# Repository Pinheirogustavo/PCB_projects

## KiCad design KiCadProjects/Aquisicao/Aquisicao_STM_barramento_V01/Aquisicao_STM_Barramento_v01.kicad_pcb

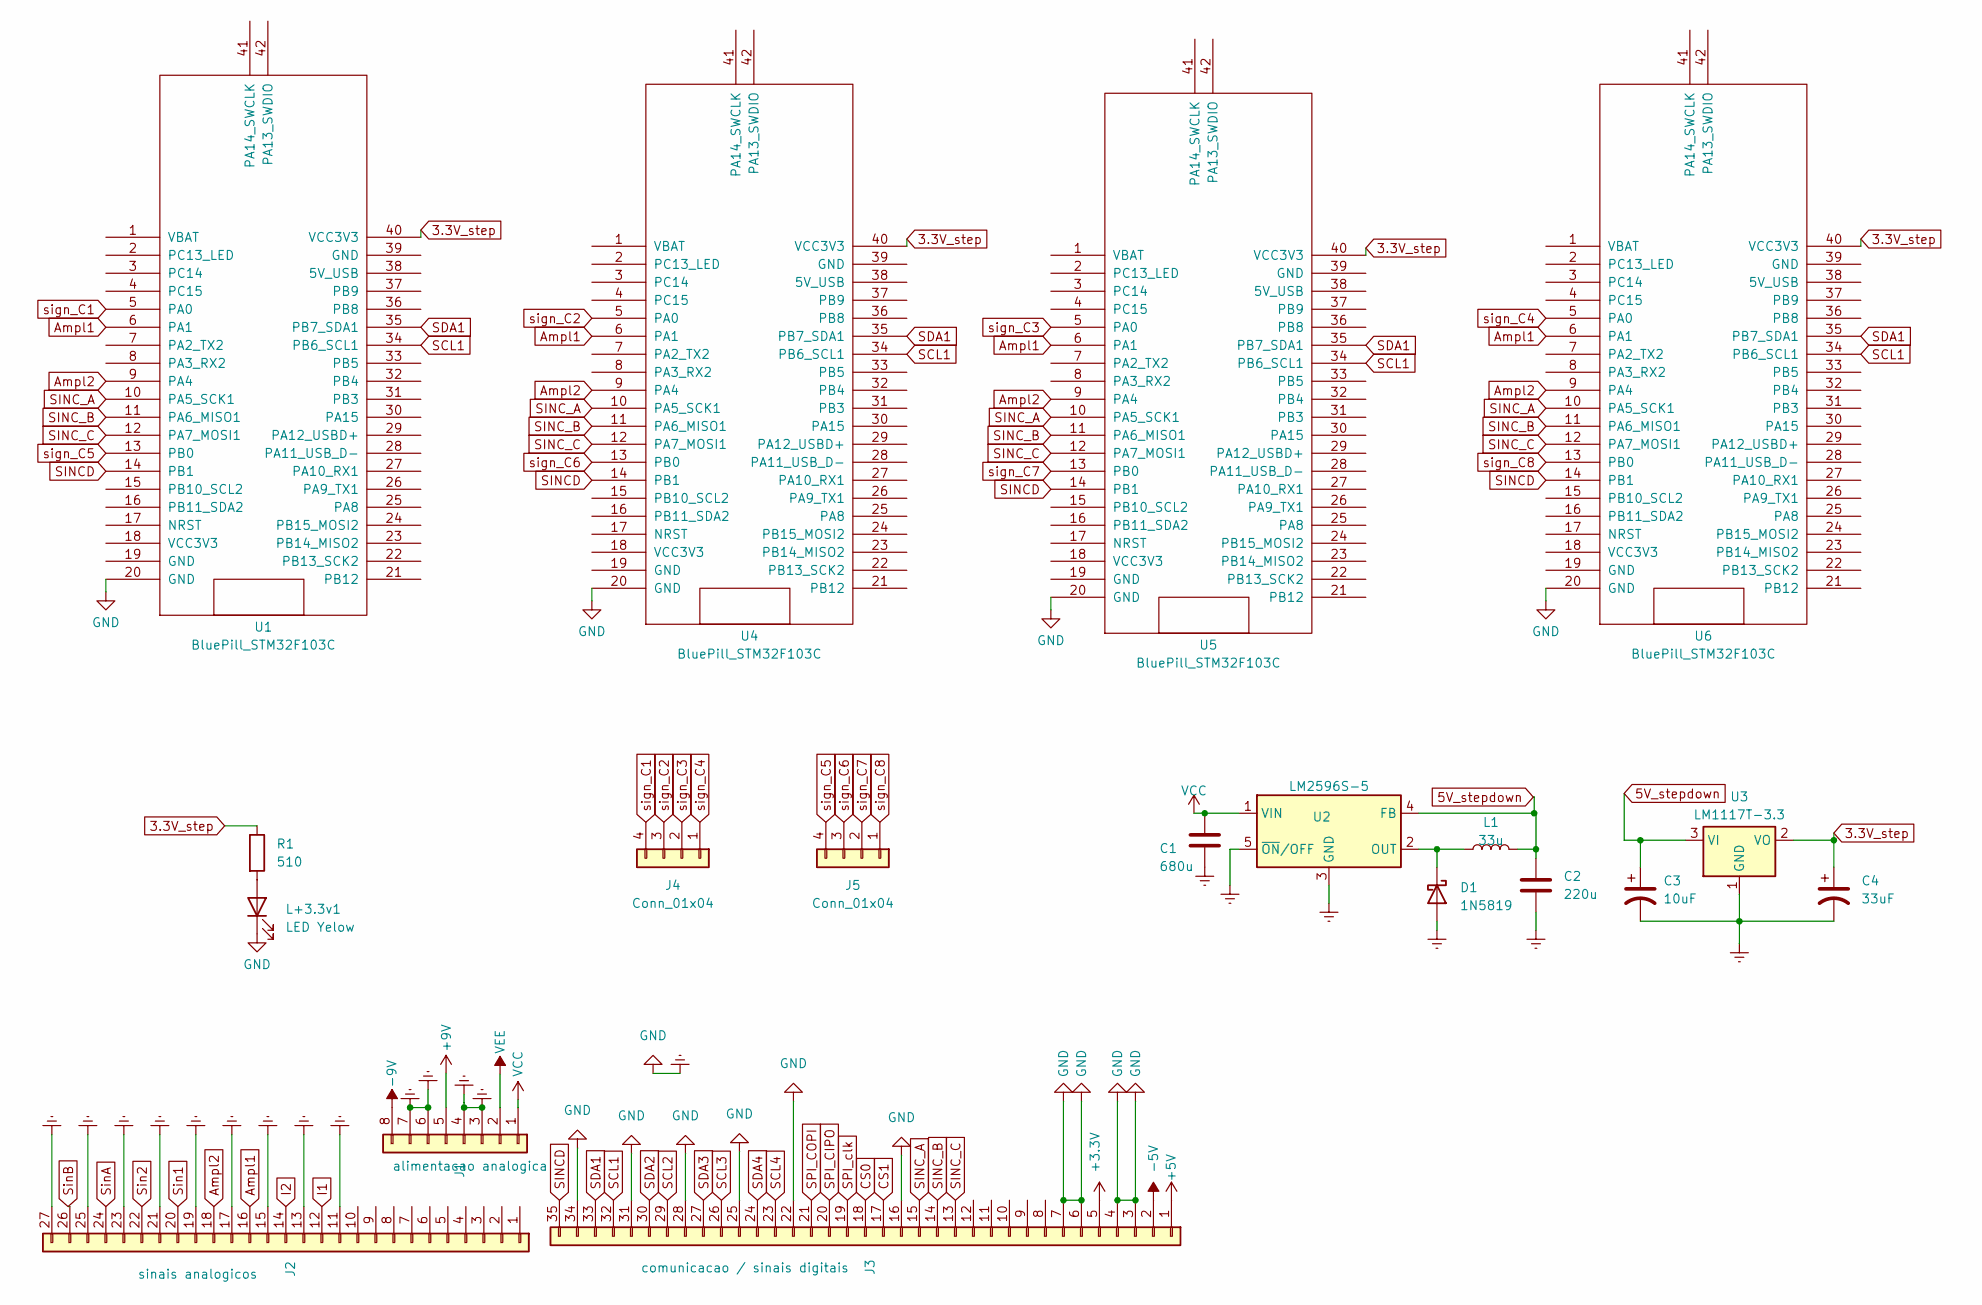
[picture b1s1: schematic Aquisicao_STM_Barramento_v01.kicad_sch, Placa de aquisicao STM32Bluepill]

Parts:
C1: 680u; CP_Radial_D5.0mm_P2.50mm
C2: 220u; CP_Radial_D5.0mm_P2.50mm
C3: 10uF; CP_Radial_Tantal_D4.5mm_P2.50mm
C4: 33uF; CP_Radial_Tantal_D4.5mm_P2.50mm
D1: 1N5819; D_DO-41_SOD81_P10.16mm_Horizontal
J1: alimentacao analogica; PinHeader_1x08_P2.54mm_Vertical
J2: sinais analogicos; PinHeader_1x27_P2.54mm_Vertical
J3: comunicacao / sinais digitais; PinHeader_1x35_P2.54mm_Vertical
J4, J5: Conn_01x04; PinHeader_1x04_P2.54mm_Horizontal
L1: 33u; L_7.3x7.3_H4.5
L+3.3v1: LED Yelow; LED_D5.0mm
R1: 510; R_Axial_DIN0207_L6.3mm_D2.5mm_P7.62mm_Horizontal
U1, U4, U5, U6: BluePill_STM32F103C
U2: LM2596S-5; TO-220-5_P3.4x3.7mm_StaggerOdd_Lead3.8mm_Vertical
U3: LM1117T-3.3; TO-220-3_Vertical

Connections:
3.3V_step: C4.1, R1.1, U1.40 (VCC3V3), U3.2 (VO), U4.40 (VCC3V3), U5.40 (VCC3V3), U6.40 (VCC3V3)
5V_stepdown: C2.1, C3.1, L1.2, U2.4 (FB), U3.3 (VI)
+3.3V: J3.5
+5V: J3.1
+9V: J1.5
-5V: J3.2
-9V: J1.8
Ampl1: J2.16, U1.6 (PA1), U4.6 (PA1), U5.6 (PA1), U6.6 (PA1)
Ampl2: J2.18, U1.9 (PA4), U4.9 (PA4), U5.9 (PA4), U6.9 (PA4)
CS0: J3.18
CS1: J3.17
Earth: C1.2, C2.2, C3.2, C4.2, D1.2 (A), J1.3, J1.4, J1.6, J1.7, J2.11, J2.13, J2.15, J2.17, J2.19, J2.21, J2.23, J2.25, J2.27, J3.3, J3.4, J3.6, J3.7, J3.16, J3.22, J3.25, J3.28, J3.31, J3.34, L+3.3v1.1 (K), U1.20 (GND), U2.3 (GND), U2.5 (~ON/OFF), U3.1 (GND), U4.20 (GND), U5.20 (GND), U6.20 (GND)
I1: J2.12
I2: J2.14
unnamed: D1.1 (K), L1.1, U2.2 (OUT)
unnamed: L+3.3v1.2 (A), R1.2
SCL1: J3.32, U1.34 (PB6_SCL1), U4.34 (PB6_SCL1), U5.34 (PB6_SCL1), U6.34 (PB6_SCL1)
SCL2: J3.29
SCL3: J3.26
SCL4: J3.23
SDA1: J3.33, U1.35 (PB7_SDA1), U4.35 (PB7_SDA1), U5.35 (PB7_SDA1), U6.35 (PB7_SDA1)
SDA2: J3.30
SDA3: J3.27
SDA4: J3.24
SINCD: J3.35, U1.14 (PB1), U4.14 (PB1), U5.14 (PB1), U6.14 (PB1)
SINC_A: J3.15, U1.10 (PA5_SCK1), U4.10 (PA5_SCK1), U5.10 (PA5_SCK1), U6.10 (PA5_SCK1)
SINC_B: J3.14, U1.11 (PA6_MISO1), U4.11 (PA6_MISO1), U5.11 (PA6_MISO1), U6.11 (PA6_MISO1)
SINC_C: J3.13, U1.12 (PA7_MOSI1), U4.12 (PA7_MOSI1), U5.12 (PA7_MOSI1), U6.12 (PA7_MOSI1)
SPI_CIPO: J3.20
SPI_COPI: J3.21
SPI_clk: J3.19
Sin1: J2.20
Sin2: J2.22
SinA: J2.24
SinB: J2.26
VCC: C1.1, J1.1, U2.1 (VIN)
VEE: J1.2
sign_C1: J4.4, U1.5 (PA0)
sign_C2: J4.3, U4.5 (PA0)
sign_C3: J4.2, U5.5 (PA0)
sign_C4: J4.1, U6.5 (PA0)
sign_C5: J5.4, U1.13 (PB0)
sign_C6: J5.3, U4.13 (PB0)
sign_C7: J5.2, U5.13 (PB0)
sign_C8: J5.1, U6.13 (PB0)

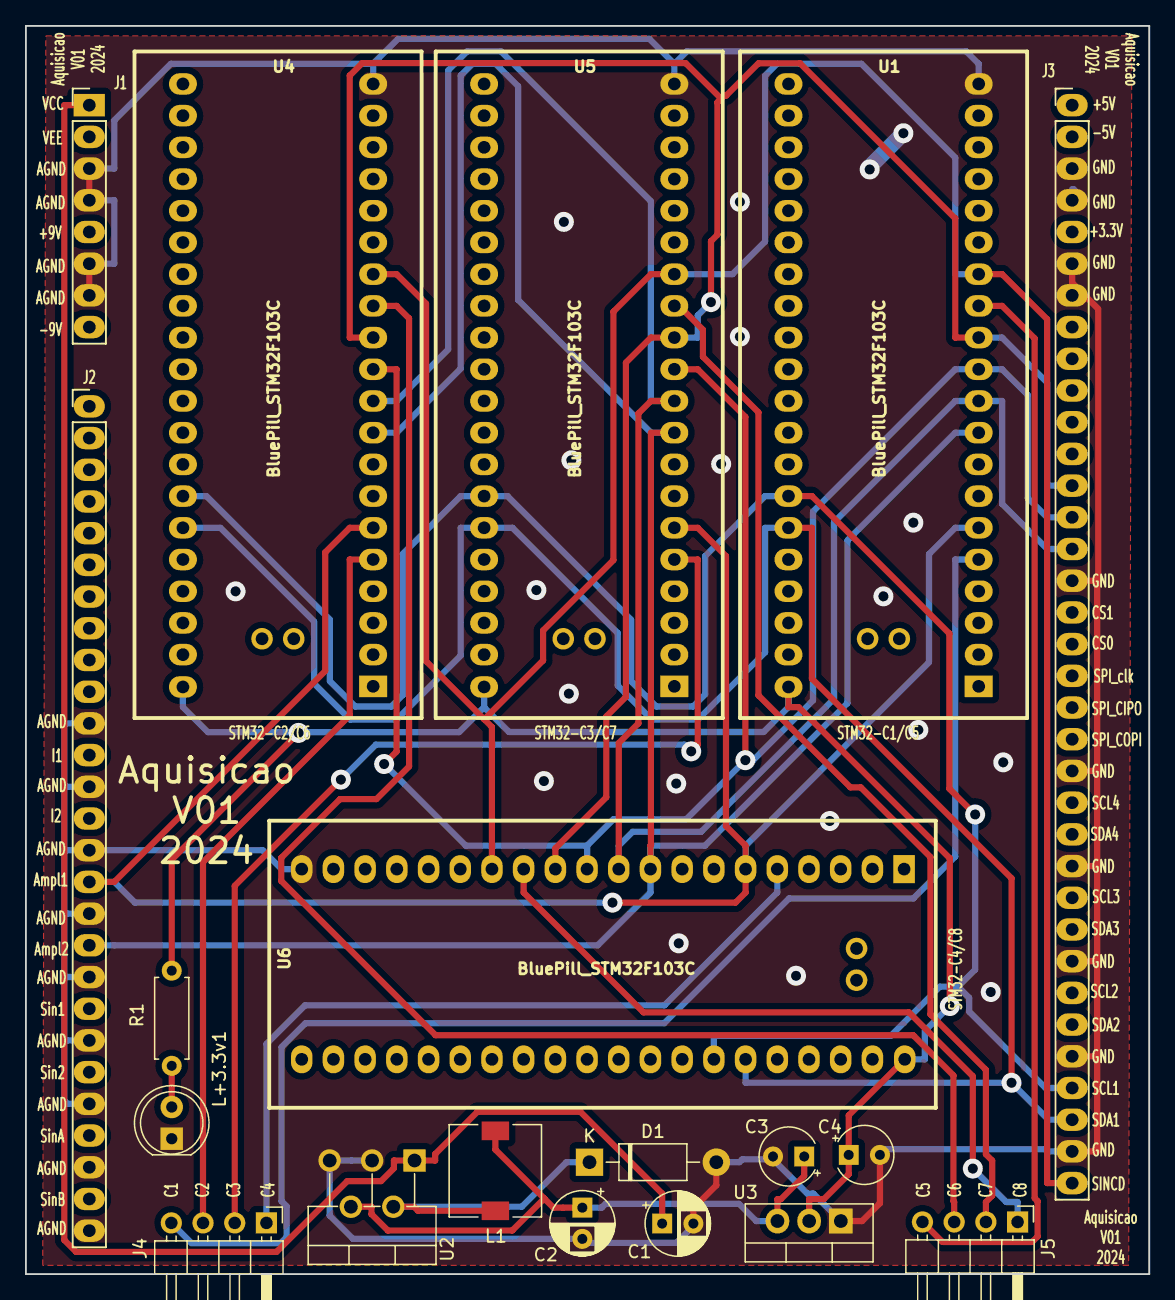
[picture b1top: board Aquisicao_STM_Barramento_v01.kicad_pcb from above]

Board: 2 copper layers, 90.0 x 100.0 mm, 19 parts (0 on the bottom side), 22 nets.

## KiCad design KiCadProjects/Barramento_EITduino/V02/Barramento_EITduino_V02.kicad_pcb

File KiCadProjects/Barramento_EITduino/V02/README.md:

# V02

- Diversos pontos de terras, separados em terras dos sinais analógicos (AGND) e terras dos sinais digitais (DGND).
- As alimentações dos circuitos analógicos foram separadas das alimentações dos circuitos digitais.

# Esquemático

![Barramento EITduino V02  colorido - Kicad](https://github.com/Pinheirogustavo/PCB_projects/blob/main/KiCadProjects/Barramento_EITduino/V02/print/barramento_v02_colorido.png

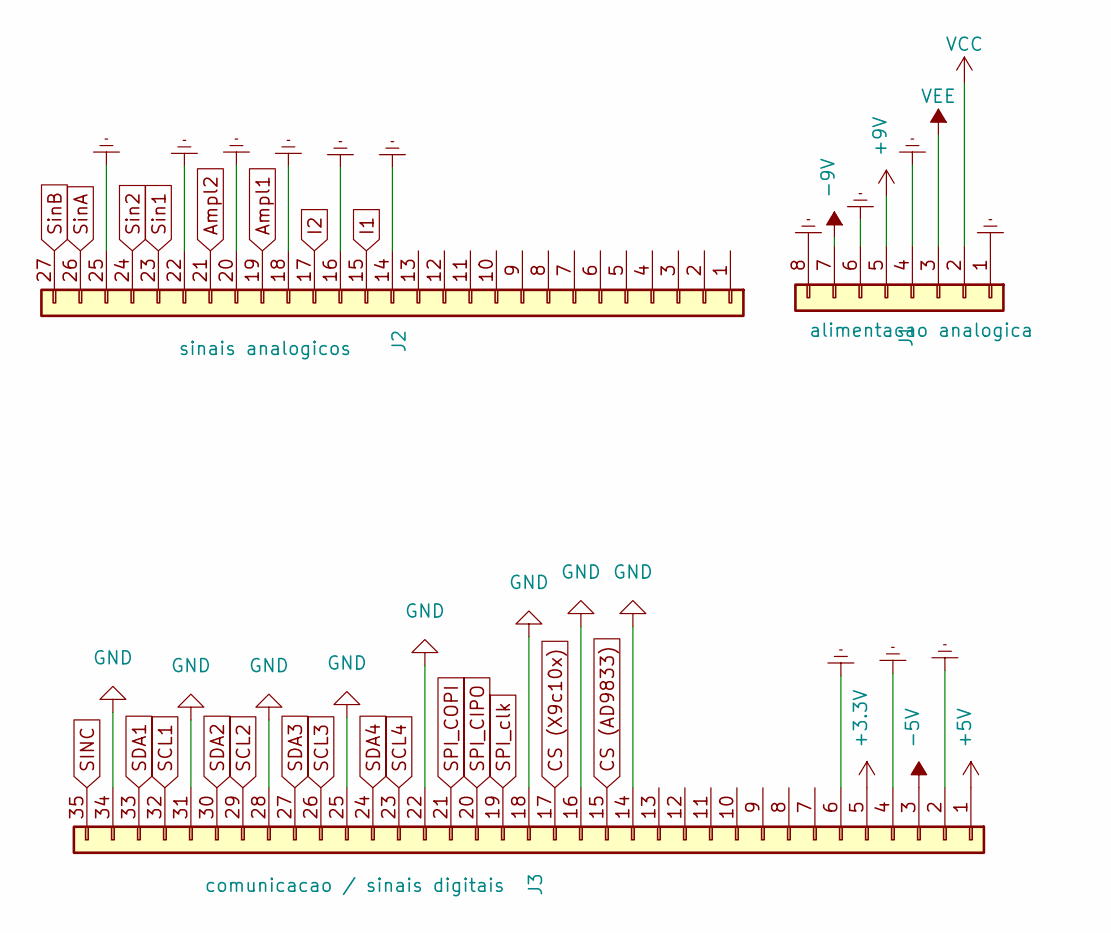
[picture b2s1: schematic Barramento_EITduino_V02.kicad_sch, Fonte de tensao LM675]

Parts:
J1: alimentacao analogica; PinHeader_1x08_P2.54mm_Vertical
J2: sinais analogicos; PinHeader_1x27_P2.54mm_Vertical
J3: comunicacao / sinais digitais; PinHeader_1x35_P2.54mm_Vertical

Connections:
+3.3V: J3.5
+5V: J3.1
+9V: J1.5
-5V: J3.3
-9V: J1.7
Ampl1: J2.19
Ampl2: J2.21
CS (AD9833): J3.15
CS (X9c10x): J3.17
Earth: J1.1, J1.4, J1.6, J1.8, J2.14, J2.16, J2.18, J2.20, J2.22, J2.25, J3.2, J3.4, J3.6
GND: J3.14, J3.16, J3.18, J3.22, J3.25, J3.28, J3.31, J3.34
I1: J2.15
I2: J2.17
SCL1: J3.32
SCL2: J3.29
SCL3: J3.26
SCL4: J3.23
SDA1: J3.33
SDA2: J3.30
SDA3: J3.27
SDA4: J3.24
SINC: J3.35
SPI_CIPO: J3.20
SPI_COPI: J3.21
SPI_clk: J3.19
Sin1: J2.23
Sin2: J2.24
SinA: J2.26
SinB: J2.27
VCC: J1.2
VEE: J1.3

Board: 2 copper layers, 3 parts (0 on the bottom side), 2 nets, no tracks yet.

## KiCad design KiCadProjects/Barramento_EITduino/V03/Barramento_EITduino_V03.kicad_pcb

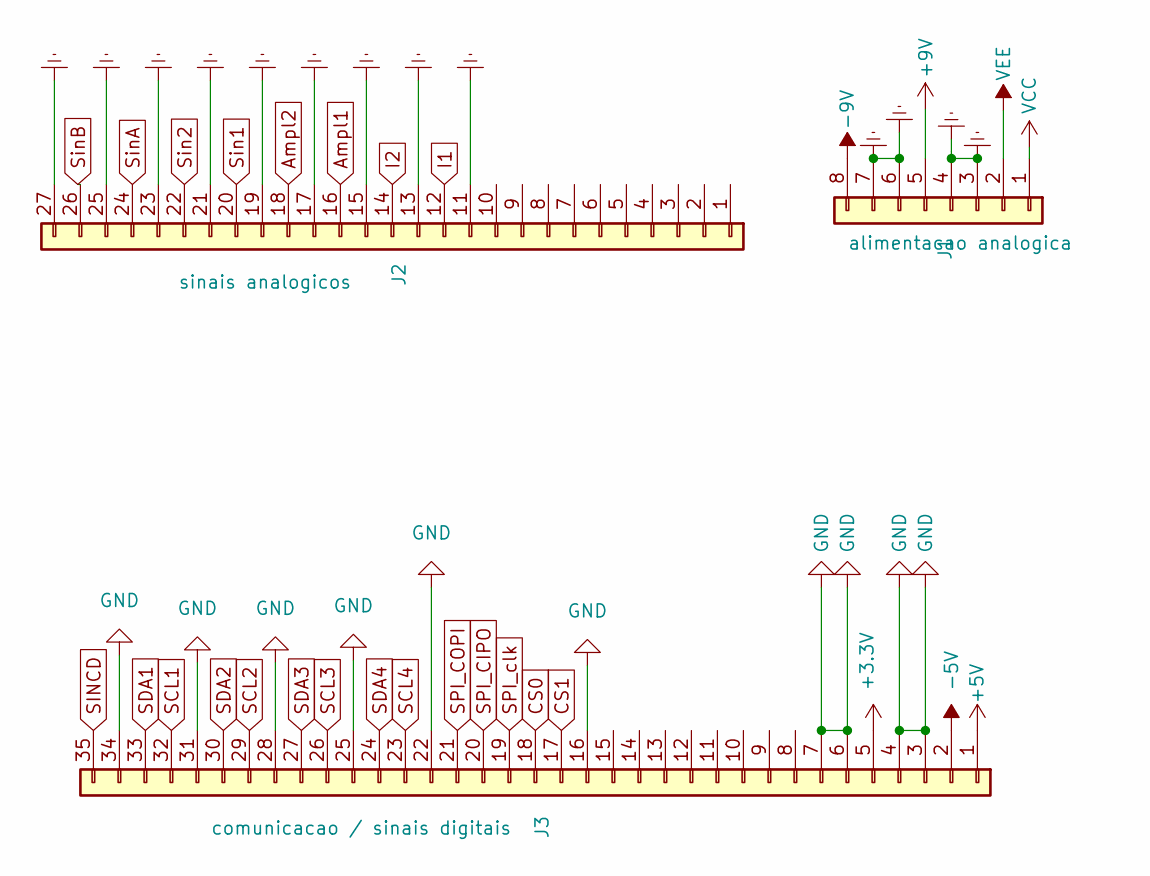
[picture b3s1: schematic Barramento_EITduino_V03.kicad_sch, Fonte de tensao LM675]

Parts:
J1: alimentacao analogica; PinHeader_1x08_P2.54mm_Vertical
J2: sinais analogicos; PinHeader_1x27_P2.54mm_Vertical
J3: comunicacao / sinais digitais; PinHeader_1x35_P2.54mm_Vertical

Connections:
+3.3V: J3.5
+5V: J3.1
+9V: J1.5
-5V: J3.2
-9V: J1.8
Ampl1: J2.16
Ampl2: J2.18
CS0: J3.18
CS1: J3.17
Earth: J1.3, J1.4, J1.6, J1.7, J2.11, J2.13, J2.15, J2.17, J2.19, J2.21, J2.23, J2.25, J2.27
GND: J3.3, J3.4, J3.6, J3.7, J3.16, J3.22, J3.25, J3.28, J3.31, J3.34
I1: J2.12
I2: J2.14
SCL1: J3.32
SCL2: J3.29
SCL3: J3.26
SCL4: J3.23
SDA1: J3.33
SDA2: J3.30
SDA3: J3.27
SDA4: J3.24
SINCD: J3.35
SPI_CIPO: J3.20
SPI_COPI: J3.21
SPI_clk: J3.19
Sin1: J2.20
Sin2: J2.22
SinA: J2.24
SinB: J2.26
VCC: J1.1
VEE: J1.2

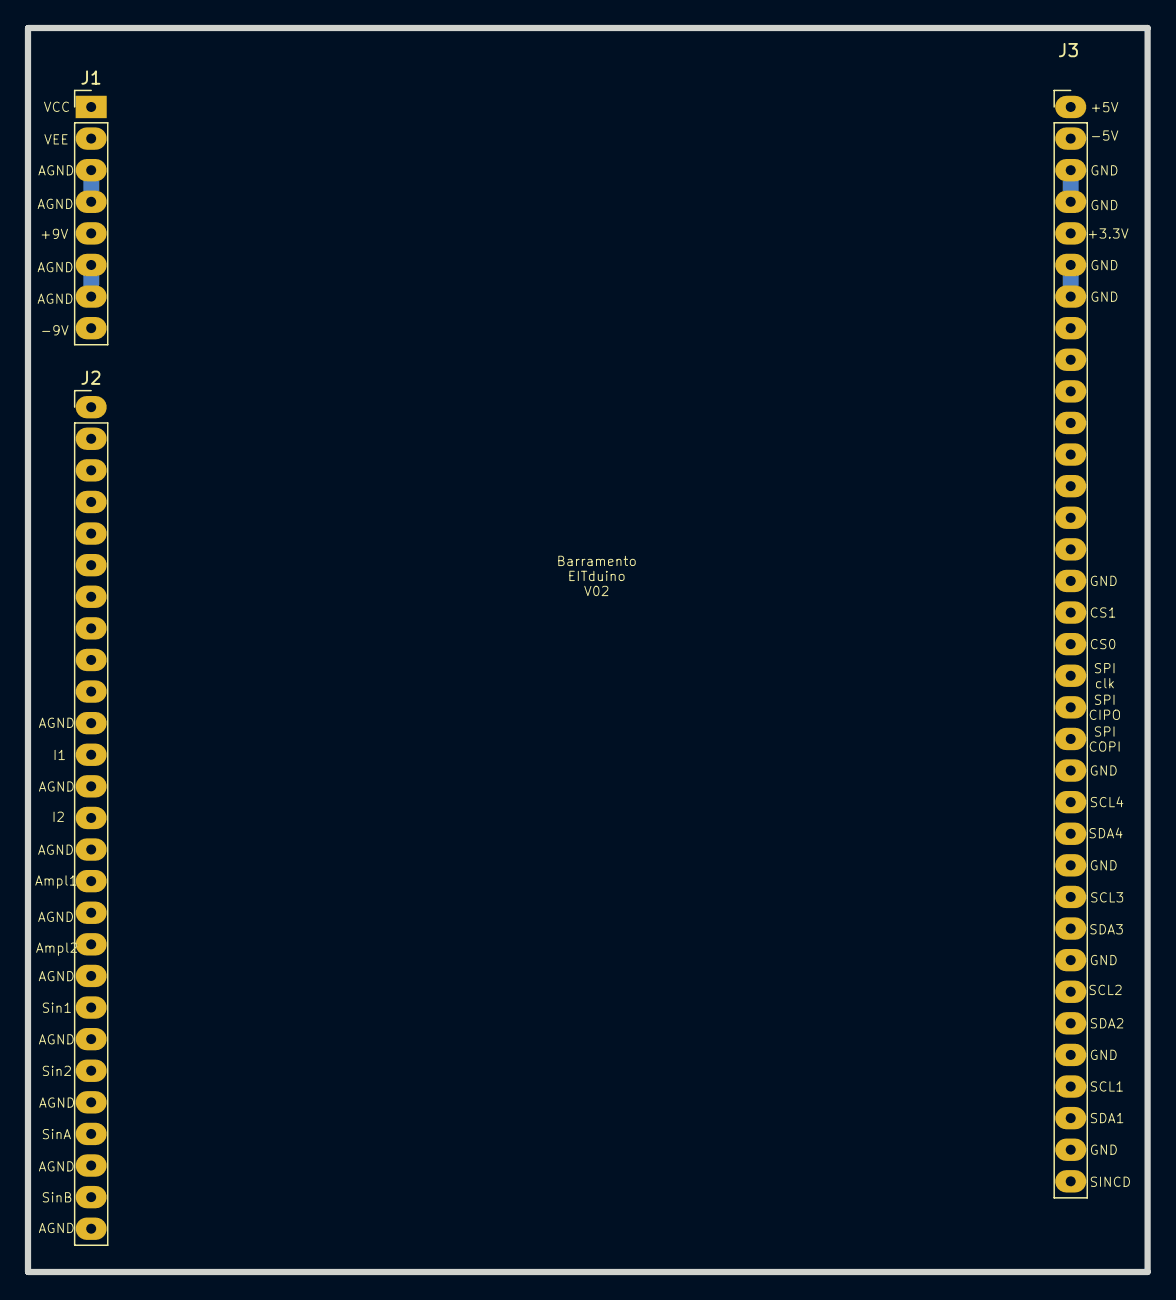
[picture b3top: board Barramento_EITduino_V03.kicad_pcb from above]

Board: 2 copper layers, 90.0 x 100.0 mm, 3 parts (0 on the bottom side), 2 nets.
